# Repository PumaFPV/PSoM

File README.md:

# PSoM
PSoM, either Pico System On Module, or Puma System On Module for those who prefer.

The goal is to have an easy to integrate MCU + BMS for any kind of projects.
Without attaching points, the SoM is 20mm*20mm. 

## PSoM_ESP32S2_00
Hardware is done and working!

## PSoM_RP2040_00
Schematic is work in progress

##PSoM_ESP32_PICOD4_00
Schematic os work on progress

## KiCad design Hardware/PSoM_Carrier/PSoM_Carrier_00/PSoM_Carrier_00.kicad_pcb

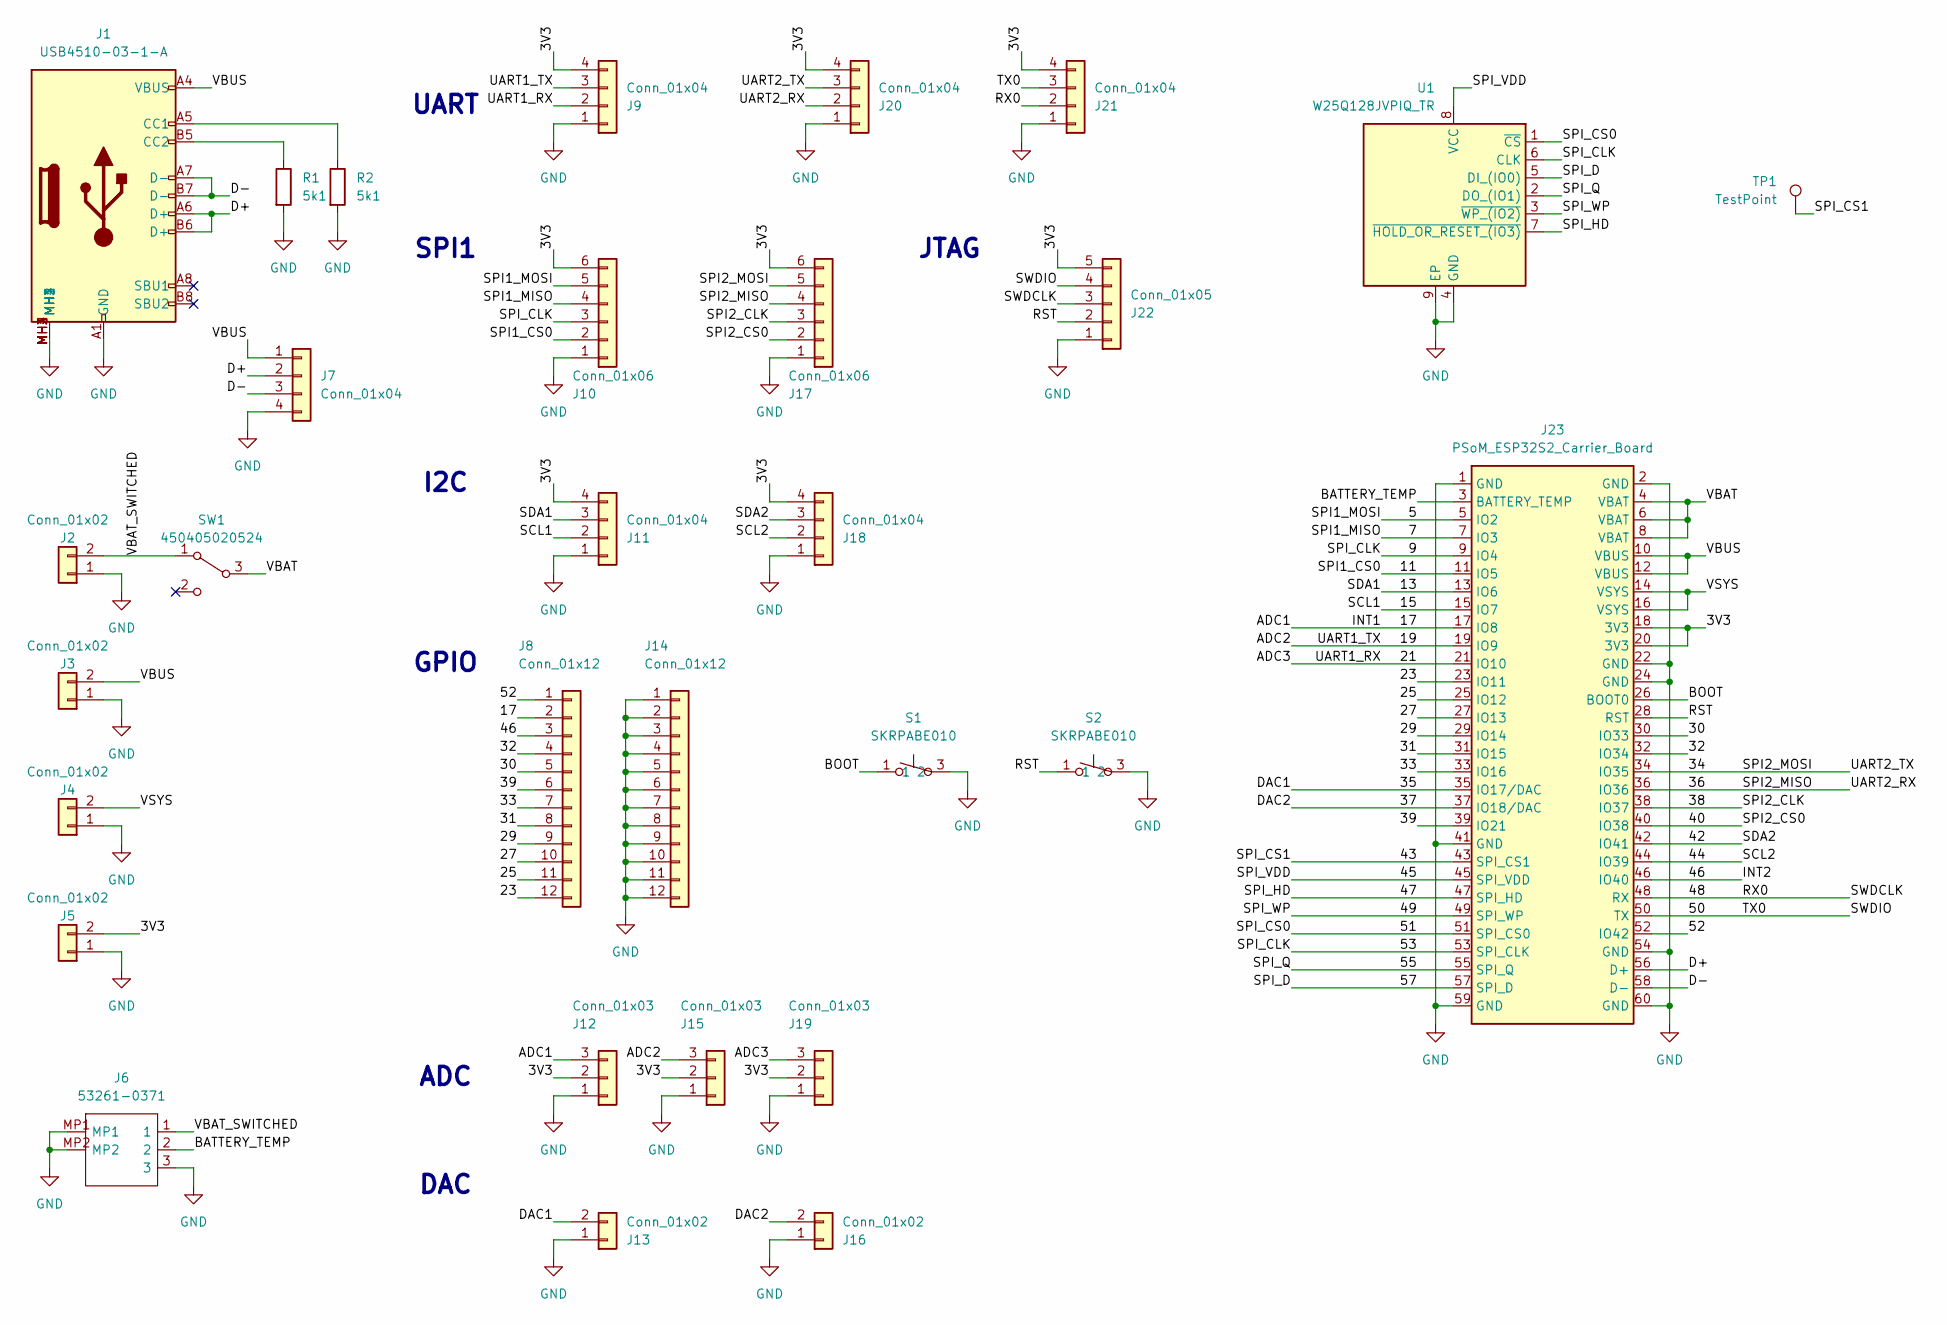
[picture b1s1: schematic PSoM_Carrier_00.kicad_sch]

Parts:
J1: USB4510-03-1-A; USB4510031A; Mouser Part Number 640-USB4510031A
J2, J3, J4, J5, J13, J16: Conn_01x02; PinHeader_1x02_P2.54mm_Vertical
J6: 53261-0371; 532610371; Mouser Part Number 538-53261-0371
J7, J9, J11, J18, J20, J21: Conn_01x04; PinHeader_1x04_P2.54mm_Vertical
J8, J14: Conn_01x12; PinHeader_1x12_P2.54mm_Vertical
J10, J17: Conn_01x06; PinHeader_1x06_P2.54mm_Vertical
J12, J15, J19: Conn_01x03; PinHeader_1x03_P2.54mm_Vertical
J22: Conn_01x05; PinHeader_1x05_P2.54mm_Vertical
J23: PSoM_ESP32S2_Carrier_Board; PSoM_ESP32S2_00
R1, R2: 5k1; R_0402_1005Metric
S1, S2: SKRPABE010; Mouser Part Number 688-SKRPAB
SW1: 450405020524
TP1: TestPoint; TestPoint_Pad_1.0x1.0mm
U1: W25Q128JVPIQ_TR; SON127P600X500X80-9N-D; Mouser Part Number 454-W25Q128JVPIQTR

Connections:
/3V3: J5.2, J9.4, J10.6, J11.4, J12.2, J15.2, J17.6, J18.4, J19.2, J20.4, J21.4, J22.5, J23.18 (3V3), J23.20 (3V3)
/5: J10.5, J23.5 (IO2)
/7: J10.4, J23.7 (IO3)
/11: J10.2, J23.11 (IO5)
/13: J11.3, J23.13 (IO6)
/15: J11.2, J23.15 (IO7)
/17: J8.2, J12.3, J23.17 (IO8)
/19: J9.3, J15.3, J23.19 (IO9)
/21: J9.2, J19.3, J23.21 (IO10)
/23: J8.12, J23.23 (IO11)
/25: J8.11, J23.25 (IO12)
/27: J8.10, J23.27 (IO13)
/29: J8.9, J23.29 (IO14)
/30: J8.5, J23.30 (IO33)
/31: J8.8, J23.31 (IO15)
/32: J8.4, J23.32 (IO34)
/33: J8.7, J23.33 (IO16)
/34: J17.5, J20.3, J23.34 (IO35)
/35: J13.2, J23.35 (IO17/DAC)
/36: J17.4, J20.2, J23.36 (IO36)
/37: J16.2, J23.37 (IO18/DAC)
/38: J17.3, J23.38 (IO37)
/39: J8.6, J23.39 (IO21)
/40: J17.2, J23.40 (IO38)
/42: J18.3, J23.42 (IO41)
/43: J23.43 (SPI_CS1), TP1.1; also elsewhere on the board
/44: J18.2, J23.44 (IO39)
/45: J23.45 (SPI_VDD), U1.8 (VCC)
/46: J8.3, J23.46 (IO40)
/47: J23.47 (SPI_HD), U1.7 (~HOLD_OR_RESET_(IO3))
/48: J21.2, J22.3, J23.48 (RX)
/49: J23.49 (SPI_WP), U1.3 (~WP_(IO2))
/50: J21.3, J22.4, J23.50 (TX)
/51: J23.51 (SPI_CS0), U1.1 (~CS)
/52: J8.1, J23.52 (IO42)
/53: J10.3, J23.9 (IO4), J23.53 (SPI_CLK), U1.6 (CLK)
/55: J23.55 (SPI_Q), U1.2 (DO_(IO1))
/57: J23.57 (SPI_D), U1.5 (DI_(IO0))
/BATTERY_TEMP: J6.2, J23.3 (BATTERY_TEMP)
/BOOT: J23.26 (BOOT0), S1.1, S1.2 (1)
/D+: J1.A6 (D+), J1.B6 (D+), J7.2, J23.56 (D+)
/D-: J1.A7 (D-), J1.B7 (D-), J7.3, J23.58 (D-)
/RST: J22.2, J23.28 (RST), S2.1, S2.2 (1)
/VBAT: J23.4 (VBAT), J23.6 (VBAT), J23.8 (VBAT), SW1.3 (B)
/VBAT_SWITCHED: J2.2, J6.1, SW1.1 (A)
/VBUS: J1.A4 (VBUS), J1.A9 (VBUS), J1.B4 (VBUS), J1.B9 (VBUS), J3.2, J7.1, J23.10 (VBUS), J23.12 (VBUS)
/VSYS: J4.2, J23.14 (VSYS), J23.16 (VSYS)
GND: J1.A1 (GND), J1.A12 (GND), J1.B1 (GND), J1.B12 (GND), J1.MH1, J1.MH2, J1.MH3, J1.MH4, J2.1, J3.1, J4.1, J5.1, J6.3, J6.MP1, J6.MP2, J7.4, J9.1, J10.1, J11.1, J12.1, J13.1, J14.1, J14.2, J14.3, J14.4, J14.5, J14.6, J14.7, J14.8, J14.9, J14.10, J14.11, J14.12, J15.1, J16.1, J17.1, J18.1, J19.1, J20.1, J21.1, J22.1, J23.1 (GND), J23.2 (GND), J23.22 (GND), J23.24 (GND), J23.41 (GND), J23.54 (GND), J23.59 (GND), J23.60 (GND), R1.2, R2.2, S1.3 (2), S1.4 (2), S2.3 (2), S2.4 (2), U1.4 (GND), U1.9 (EP)
unnamed: J1.A5 (CC1), R2.1
unnamed: J1.B5 (CC2), R1.1

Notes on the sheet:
ADC
DAC
I2C
JTAG
SPI1
GPIO
UART

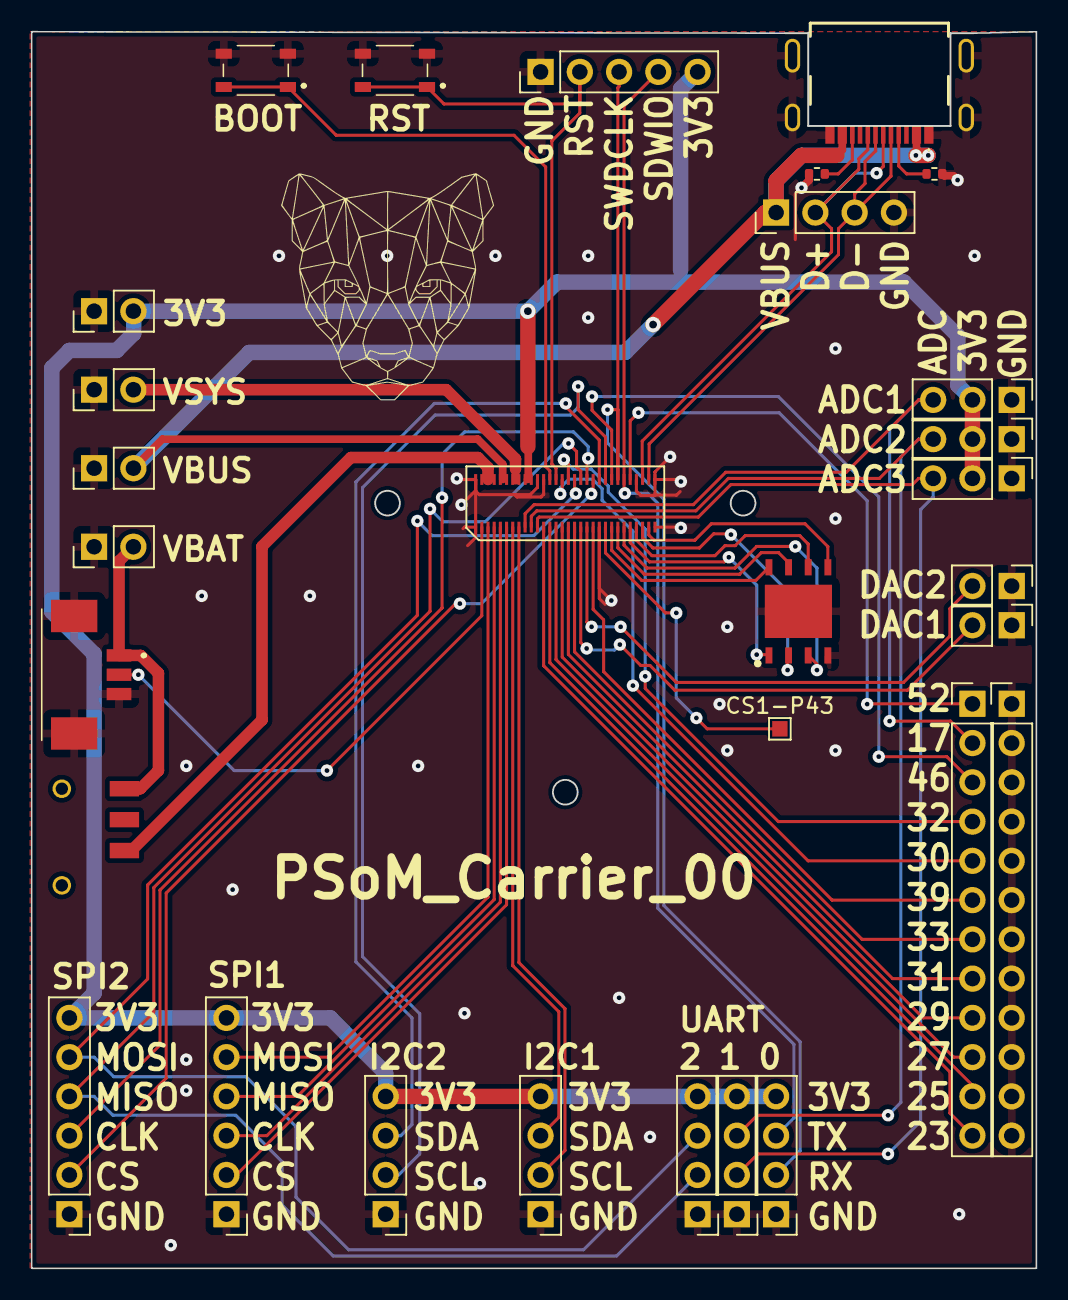
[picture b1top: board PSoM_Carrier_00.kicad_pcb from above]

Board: 2 copper layers, 65.0 x 80.0 mm, 30 parts (0 on the bottom side), 50 nets.

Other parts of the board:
CS1-P43: TestPoint; TestPoint_Pad_1.0x1.0mm

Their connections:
/43: CS1-P43.1; also elsewhere on the board

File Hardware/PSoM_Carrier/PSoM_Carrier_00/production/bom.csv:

Designator,Footprint,Quantity,Value,LCSC Part #
CS1-P43,TestPoint_Pad_1.0x1.0mm,1,TestPoint,
J1,USB4510031A,1,USB4510-03-1-A,
"J10, J17",PinHeader_1x06_P2.54mm_Vertical,2,Conn_01x06,
"J11, J18, J20, J21, J7, J9",PinHeader_1x04_P2.54mm_Vertical,6,Conn_01x04,
"J12, J15, J19",PinHeader_1x03_P2.54mm_Vertical,3,Conn_01x03,
"J13, J16, J2, J3, J4, J5",PinHeader_1x02_P2.54mm_Vertical,6,Conn_01x02,
"J14, J8",PinHeader_1x12_P2.54mm_Vertical,2,Conn_01x12,
J22,PinHeader_1x05_P2.54mm_Vertical,1,Conn_01x05,
J23,PSoM_ESP32S2_00,1,PSoM_ESP32S2_Carrier_Board,
J6,532610371,1,53261-0371,
"R1, R2",0402,2,5k1,
"S1, S2",SKRPABE010,2,SKRPABE010,
SW1,450405020524,1,450405020524,
U1,SON127P600X500X80-9N-D,1,W25Q128JVPIQ_TR,

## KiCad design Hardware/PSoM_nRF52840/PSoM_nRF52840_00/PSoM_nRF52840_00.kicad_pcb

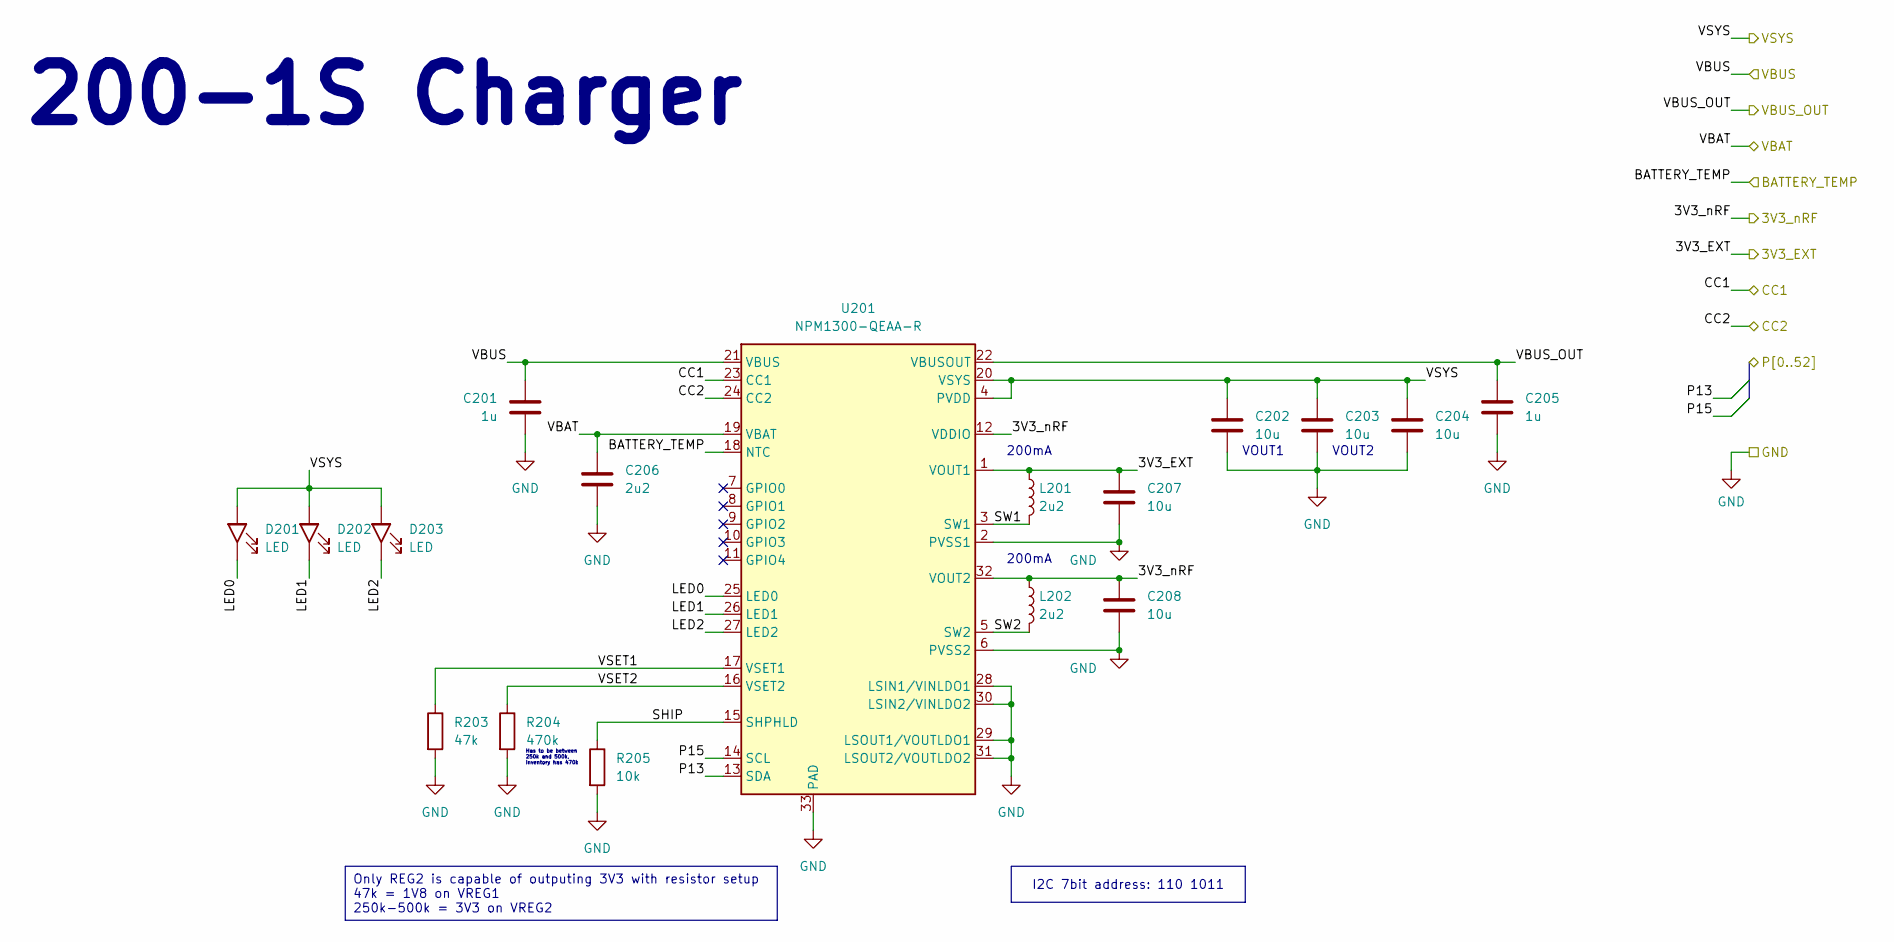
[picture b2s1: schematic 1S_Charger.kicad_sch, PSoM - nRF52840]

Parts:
C201, C205: 1u; C_0402_1005Metric
C202, C203, C204: 10u; C_0603_1608Metric
C206: 2u2; C_0603_1608Metric
C207: 10u; C_0402_1005Metric
C208: 10u; C_0402_1005Metric_Pad0.74x0.62mm_HandSolder
D201, D202, D203: LED; LED_0402_1005Metric
L201, L202: 2u2; L_0603_1608Metric
R203: 47k; R_0201_0603Metric
R204: 470k; R_0201_0603Metric
R205: 10k; R_0201_0603Metric
U201: NPM1300-QEAA-R; Mouser Part Number 949-NPM1300-QEAA-R

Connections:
+3V3: C207.1, L201.1, U201.1 (VOUT1); also elsewhere on the board
/100_Connectors/BATTERY_TEMP: U201.18 (NTC); also elsewhere on the board
/100_Connectors/CC1: U201.23 (CC1); also elsewhere on the board
/100_Connectors/CC2: U201.24 (CC2); also elsewhere on the board
/100_Connectors/VBAT: C206.1, U201.19 (VBAT); also elsewhere on the board
/100_Connectors/VSYS: C202.1, C203.1, C204.1, D201.1 (A), D202.1 (A), D203.1 (A), U201.4 (PVDD), U201.20 (VSYS); also elsewhere on the board
/200_1S_Charger/3V3_nRF: C208.1, L202.1, U201.12 (VDDIO), U201.32 (VOUT2); also elsewhere on the board
/200_1S_Charger/LED0: D201.2 (K), U201.25 (LED0)
/200_1S_Charger/LED1: D202.2 (K), U201.26 (LED1)
/200_1S_Charger/LED2: D203.2 (K), U201.27 (LED2)
/200_1S_Charger/SHIP: R205.1, U201.15 (SHPHLD)
/200_1S_Charger/SW1: L201.2, U201.3 (SW1)
/200_1S_Charger/SW2: L202.2, U201.5 (SW2)
/200_1S_Charger/VBUS_OUT: C205.1, U201.22 (VBUSOUT); also elsewhere on the board
/200_1S_Charger/VSET1: R203.1, U201.17 (VSET1)
/200_1S_Charger/VSET2: R204.1, U201.16 (VSET2)
GND: C201.1, C202.2, C203.2, C204.2, C205.2, C206.2, C207.2, C208.2, R203.2, R204.2, R205.2, U201.2 (PVSS1), U201.6 (PVSS2), U201.28 (LSIN1/VINLDO1), U201.29 (LSOUT1/VOUTLDO1), U201.30 (LSIN2/VINLDO2), U201.31 (LSOUT2/VOUTLDO2), U201.33 (PAD); also elsewhere on the board
P13: U201.13 (SDA); also elsewhere on the board
P15: U201.14 (SCL); also elsewhere on the board
VBUS: C201.2, U201.21 (VBUS); also elsewhere on the board

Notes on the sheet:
Only REG2 is capable of outputing 3V3 with resistor setup 47k = 1V8 on VREG1 250k-500k = 3V3 on VREG2
I2C 7bit address: 110 1011
200-1S Charger
200mA
Has to be between 250k and 500k, Inventory has 470k
VOUT1
VOUT2

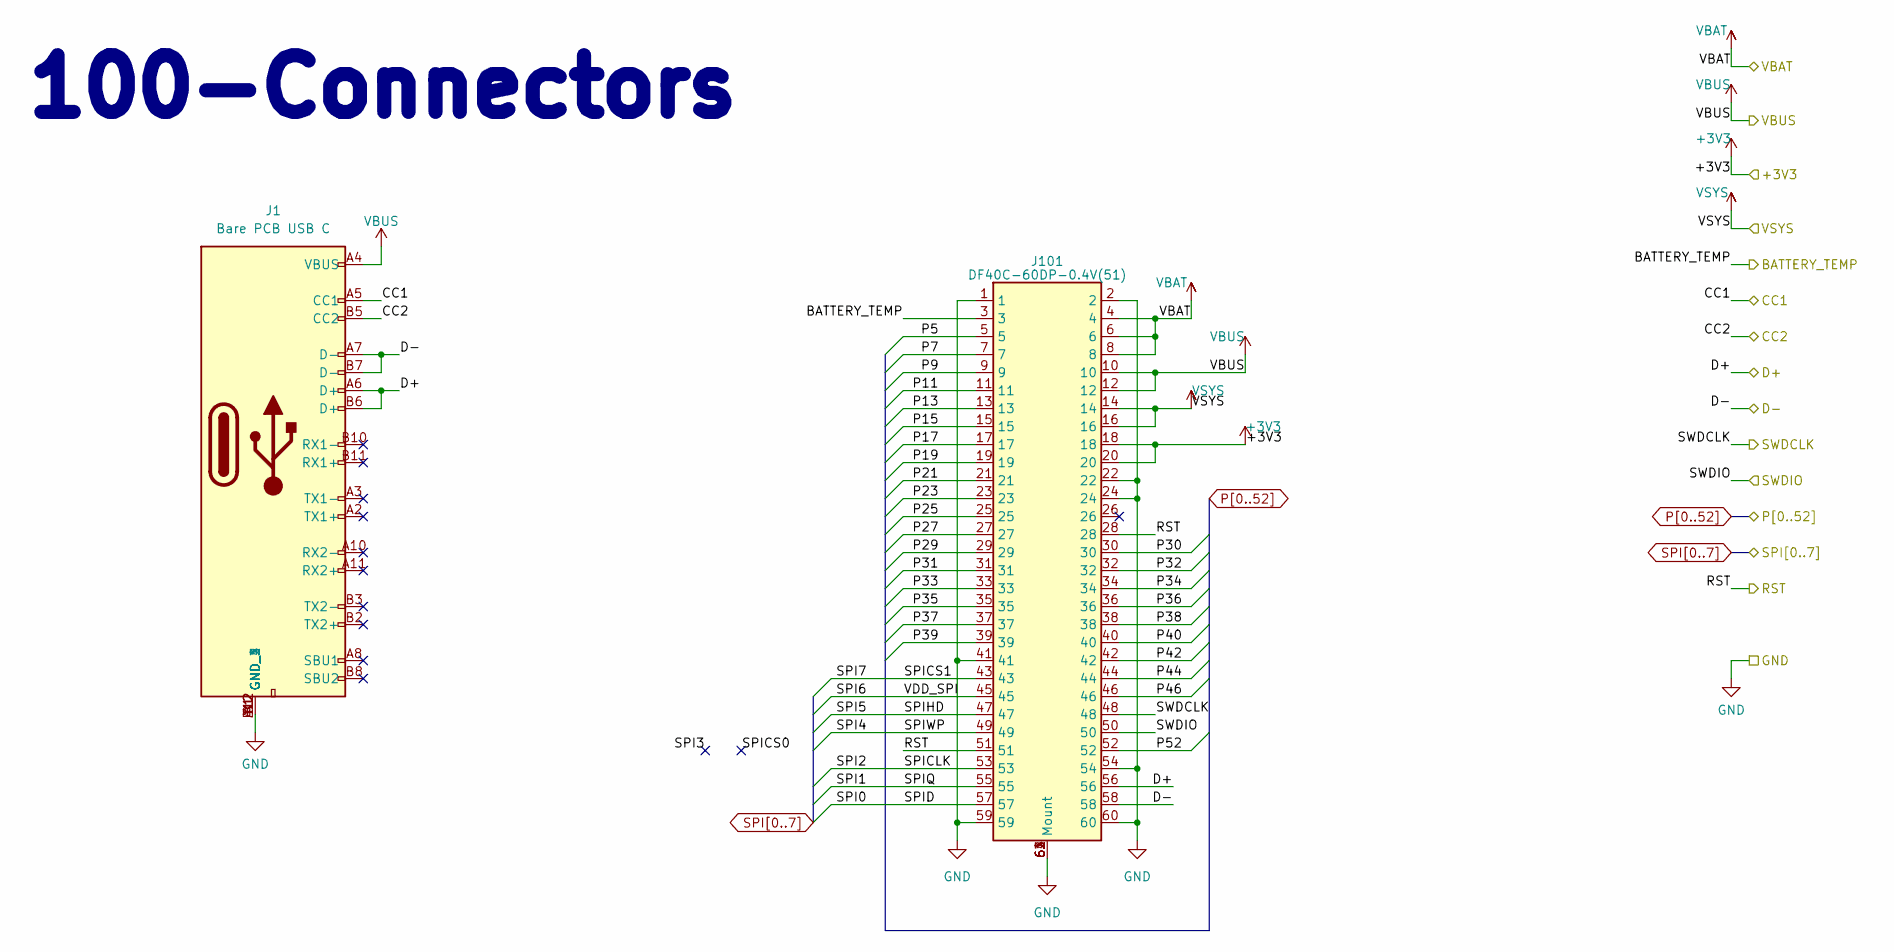
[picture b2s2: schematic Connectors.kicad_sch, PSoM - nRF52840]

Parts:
J1: Bare PCB USB C; usb-c-pcb; Mouser Part Number 640-USB4510031A
J101: DF40C-60DP-0.4V(51)

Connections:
+3V3: J101.18, J101.20; also elsewhere on the board
/100_Connectors/BATTERY_TEMP: J101.3; also elsewhere on the board
/100_Connectors/CC1: J1.A5 (CC1); also elsewhere on the board
/100_Connectors/CC2: J1.B5 (CC2); also elsewhere on the board
/100_Connectors/D+: J1.A6 (D+), J1.B6 (D+), J101.56; also elsewhere on the board
/100_Connectors/D-: J1.A7 (D-), J1.B7 (D-), J101.58; also elsewhere on the board
/100_Connectors/RST: J101.28, J101.51; also elsewhere on the board
/100_Connectors/SWDCLK: J101.48; also elsewhere on the board
/100_Connectors/SWDIO: J101.50; also elsewhere on the board
/100_Connectors/VBAT: J101.4, J101.6, J101.8; also elsewhere on the board
/100_Connectors/VSYS: J101.14, J101.16; also elsewhere on the board
GND: J1.A1 (GND_1), J1.A12 (GND_2), J1.B1 (GND_3), J1.B12 (GND_4), J101.1, J101.2, J101.22, J101.24, J101.41, J101.54, J101.59, J101.60, J101.61 (Mount), J101.62, J101.63, J101.64; also elsewhere on the board
P5: J101.5; also elsewhere on the board
P7: J101.7; also elsewhere on the board
P9: J101.9; also elsewhere on the board
P11: J101.11; also elsewhere on the board
P13: J101.13; also elsewhere on the board
P15: J101.15; also elsewhere on the board
P17: J101.17; also elsewhere on the board
P19: J101.19; also elsewhere on the board
P21: J101.21; also elsewhere on the board
P23: J101.23; also elsewhere on the board
P25: J101.25; also elsewhere on the board
P27: J101.27; also elsewhere on the board
P29: J101.29; also elsewhere on the board
P30: J101.30; also elsewhere on the board
P31: J101.31; also elsewhere on the board
P32: J101.32; also elsewhere on the board
P33: J101.33; also elsewhere on the board
P34: J101.34; also elsewhere on the board
P35: J101.35; also elsewhere on the board
P36: J101.36; also elsewhere on the board
P37: J101.37; also elsewhere on the board
P38: J101.38; also elsewhere on the board
P39: J101.39; also elsewhere on the board
P40: J101.40; also elsewhere on the board
P42: J101.42; also elsewhere on the board
P44: J101.44; also elsewhere on the board
P46: J101.46; also elsewhere on the board
P52: J101.52; also elsewhere on the board
SPI0: J101.57; also elsewhere on the board
SPI1: J101.55; also elsewhere on the board
SPI2: J101.53; also elsewhere on the board
SPI4: J101.49; also elsewhere on the board
SPI5: J101.47; also elsewhere on the board
SPI6: J101.45
SPI7: J101.43; also elsewhere on the board
VBUS: J1.A4 (VBUS), J1.A9 (VBUS), J1.B4 (VBUS), J1.B9 (VBUS), J101.10, J101.12; also elsewhere on the board

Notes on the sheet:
100-Connectors

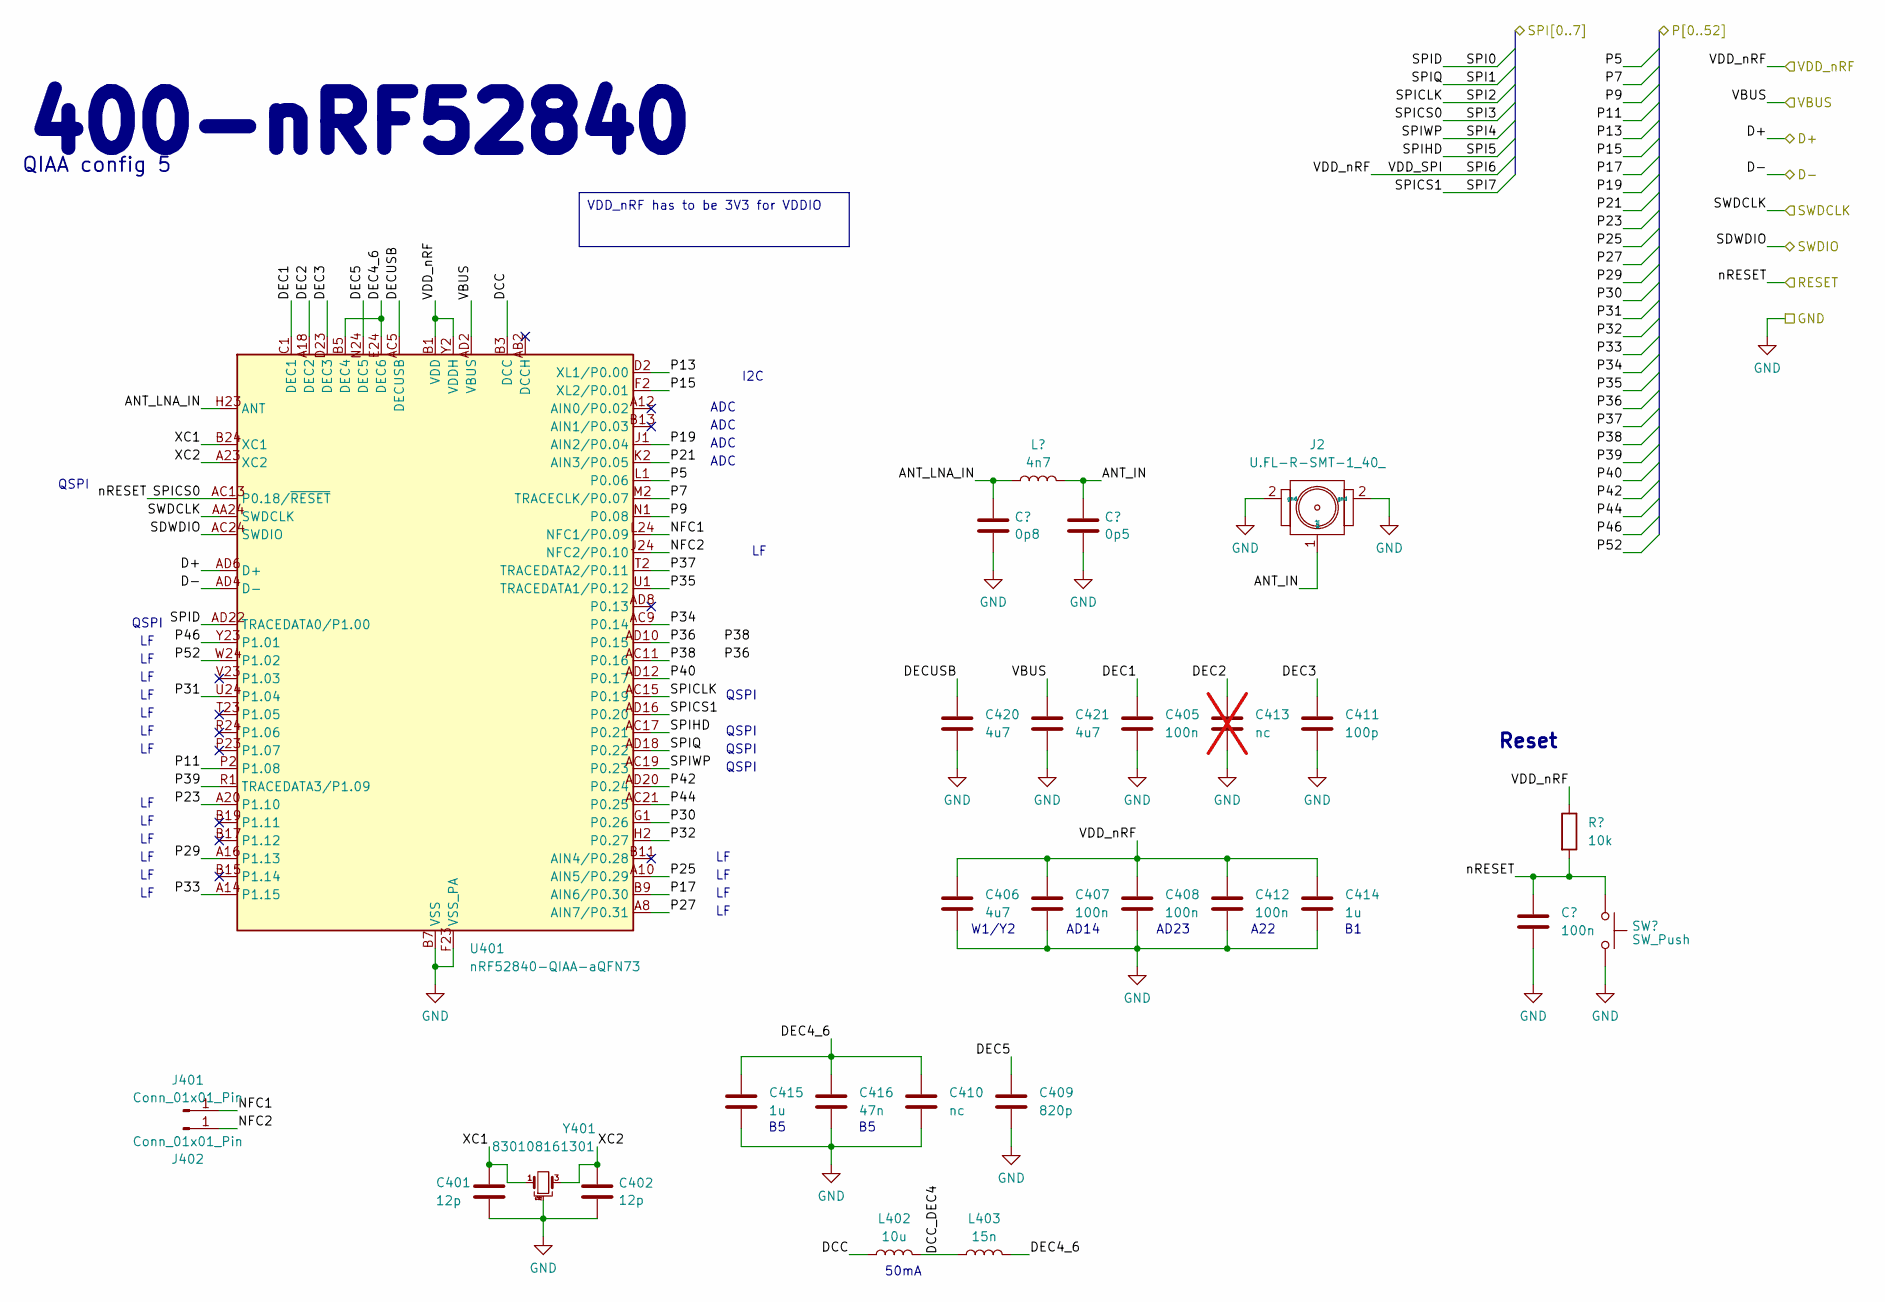
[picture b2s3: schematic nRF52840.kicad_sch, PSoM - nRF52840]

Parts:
C401, C402: 12p; C_0201_0603Metric
C403: 0p8; C_0201_0603Metric
C404: 0p5; C_0201_0603Metric
C405, C407, C408, C412, C461: 100n; C_0201_0603Metric
C406, C420, C421: 4u7; C_0603_1608Metric
C409: 820p; C_0201_0603Metric
C410: nc; C_0402_1005Metric
C411: 100p; C_0201_0603Metric
C413: nc; C_0402_1005Metric; not fitted
C414, C415: 1u; C_0402_1005Metric
C416: 47n; C_0402_1005Metric
J2: U.FL-R-SMT-1_40_; u.fl; Mouser Part Number 798-UFLRSMT140
J401, J402: Conn_01x01_Pin; SolderWirePad_1x01_SMD_1x2mm
L401: 4n7; L_0201_0603Metric
L402: 10u; L_0603_1608Metric
L403: 15n; L_0402_1005Metric
R461: 10k; R_0201_0603Metric
SW461: SW_Push; B3U-1000P
U401: nRF52840-QIAA-aQFN73; Nordic_AQFN-73-1EP_7x7mm_P0.5mm
Y401: 830108161301; 830108161301_1.6x1.2mm

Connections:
/100_Connectors/D+: U401.AD6 (D+); also elsewhere on the board
/100_Connectors/D-: U401.AD4 (D-); also elsewhere on the board
/100_Connectors/RST: C461.1, R461.2, SW461.1, U401.AC13 (P0.18/~RESET); also elsewhere on the board
/100_Connectors/SWDCLK: U401.AA24 (SWDCLK); also elsewhere on the board
/100_Connectors/SWDIO: U401.AC24 (SWDIO); also elsewhere on the board
/200_1S_Charger/3V3_nRF: C406.1, C407.1, C408.1, C412.1, C414.1, R461.1, U401.A22 (VDD), U401.AD14 (VDD), U401.AD23 (VDD), U401.B1 (VDD), U401.W1 (VDD), U401.Y2 (VDDH); also elsewhere on the board
/200_1S_Charger/VBUS_OUT: C421.1, U401.AD2 (VBUS); also elsewhere on the board
/400-nRF52840/ANT_IN: C404.1, J2.1 (ant), L401.1
/400-nRF52840/ANT_LNA_IN: C403.1, L401.2, U401.H23 (ANT)
/400-nRF52840/DCC: L402.1, U401.B3 (DCC)
/400-nRF52840/DCC_DEC4: L402.2, L403.1
/400-nRF52840/DEC1: C405.1, U401.C1 (DEC1)
/400-nRF52840/DEC2: C413.1, U401.A18 (DEC2)
/400-nRF52840/DEC3: C411.1, U401.D23 (DEC3)
/400-nRF52840/DEC4_6: C410.1, C415.1, C416.1, L403.2, U401.B5 (DEC4), U401.E24 (DEC6)
/400-nRF52840/DEC5: C409.1, U401.N24 (DEC5)
/400-nRF52840/DECUSB: C420.1, U401.AC5 (DECUSB)
/400-nRF52840/NFC1: J401.1, U401.L24 (NFC1/P0.09)
/400-nRF52840/NFC2: J402.1, U401.J24 (NFC2/P0.10)
/400-nRF52840/XC1: C401.1, U401.B24 (XC1), Y401.1
/400-nRF52840/XC2: C402.1, U401.A23 (XC2), Y401.3
GND: C401.2, C402.2, C403.2, C404.2, C405.2, C406.2, C407.2, C408.2, C409.2, C410.2, C411.2, C412.2, C413.2, C414.2, C415.2, C416.2, C420.2, C421.2, C461.2, J2.2 (gnd), SW461.2, U401.B7 (VSS), U401.EP (VSS), U401.F23 (VSS_PA), Y401.2, Y401.4; also elsewhere on the board
P5: U401.L1 (P0.06); also elsewhere on the board
P7: U401.M2 (TRACECLK/P0.07); also elsewhere on the board
P9: U401.N1 (P0.08); also elsewhere on the board
P11: U401.P2 (P1.08); also elsewhere on the board
P13: U401.D2 (XL1/P0.00); also elsewhere on the board
P15: U401.F2 (XL2/P0.01); also elsewhere on the board
P17: U401.B9 (AIN6/P0.30); also elsewhere on the board
P19: U401.J1 (AIN2/P0.04); also elsewhere on the board
P21: U401.K2 (AIN3/P0.05); also elsewhere on the board
P23: U401.A20 (P1.10); also elsewhere on the board
P25: U401.A10 (AIN5/P0.29); also elsewhere on the board
P27: U401.A8 (AIN7/P0.31); also elsewhere on the board
P29: U401.A16 (P1.13); also elsewhere on the board
P30: U401.G1 (P0.26); also elsewhere on the board
P31: U401.U24 (P1.04); also elsewhere on the board
P32: U401.H2 (P0.27); also elsewhere on the board
P33: U401.A14 (P1.15); also elsewhere on the board
P34: U401.AC9 (P0.14); also elsewhere on the board
P35: U401.U1 (TRACEDATA1/P0.12); also elsewhere on the board
P36: U401.AD10 (P0.15); also elsewhere on the board
P37: U401.T2 (TRACEDATA2/P0.11); also elsewhere on the board
P38: U401.AC11 (P0.16); also elsewhere on the board
P39: U401.R1 (TRACEDATA3/P1.09); also elsewhere on the board
P40: U401.AD12 (P0.17); also elsewhere on the board
P42: U401.AD20 (P0.24); also elsewhere on the board
P44: U401.AC21 (P0.25); also elsewhere on the board
P46: U401.Y23 (P1.01); also elsewhere on the board
P52: U401.W24 (P1.02); also elsewhere on the board
SPI0: U401.AD22 (TRACEDATA0/P1.00); also elsewhere on the board
SPI1: U401.AD18 (P0.22); also elsewhere on the board
SPI2: U401.AC15 (P0.19); also elsewhere on the board
SPI4: U401.AC19 (P0.23); also elsewhere on the board
SPI5: U401.AC17 (P0.21); also elsewhere on the board
SPI7: U401.AD16 (P0.20); also elsewhere on the board

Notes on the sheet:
VDD_nRF has to be 3V3 for VDDIO
I2C
ADC
AD23
QSPI
Reset
A22
400-nRF52840
50mA
W1/Y2
AD14
QIAA config 5

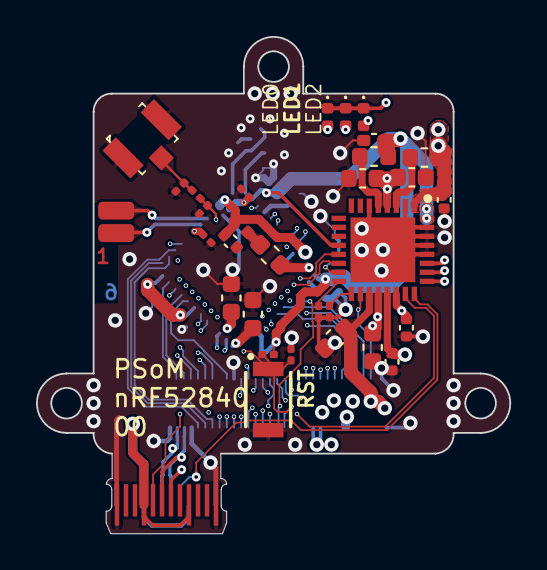
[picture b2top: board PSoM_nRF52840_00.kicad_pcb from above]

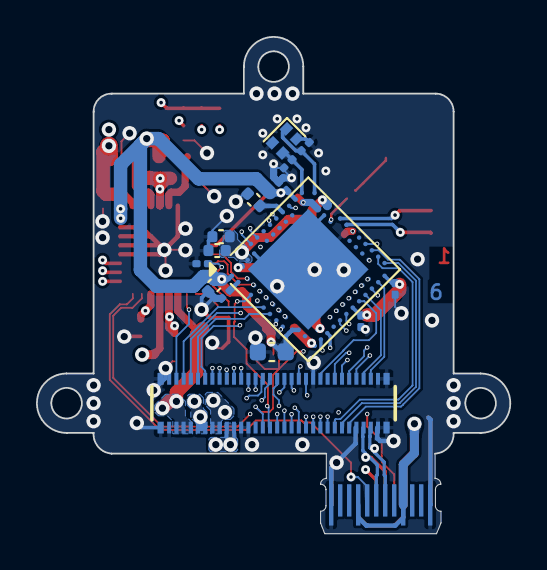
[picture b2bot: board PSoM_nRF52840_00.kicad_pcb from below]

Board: 6 copper layers, 26.3 x 27.6 mm, 48 parts (15 on the bottom side), 71 nets.

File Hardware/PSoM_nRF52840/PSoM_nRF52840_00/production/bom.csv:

Designator,Footprint,Quantity,Value,LCSC Part #
"C201, C205, C414, C415",0402,4,1u,
"C202, C203, C204, L402",0603,4,10u,
"C206, L201, L202",0603,3,2u2,
"C207, C208",0402,2,10u,
"C401, C402",0201,2,12p,
C403,0201,1,0p8,
C404,0201,1,0p5,
"C405, C407, C408, C412, C461",0201,5,100n,
"C406, C420, C421",0603,3,4u7,
C409,0201,1,820p,
"C410, C413",0402,2,nc,
C411,0201,1,100p,
C416,0402,1,47n,
"D201, D202, D203",0402,3,LED,
J1,usb-c-pcb,1,Bare PCB USB C,
J101,DF40C-60DP-0.4V(51),1,DF40C-60DP-0.4V(51),
J2,u.fl,1,U.FL-R-SMT-1_40_,
"J401, J402",SolderWirePad_1x01_SMD_1x2mm,2,Conn_01x01_Pin,
L401,0201,1,4n7,
L403,0402,1,15n,
R203,0201,1,47k,
R204,0201,1,470k,
"R205, R461",0201,2,10k,
SW461,B3U-1000P,1,SW_Push,
U201,NPM1300-QEAA-R,1,NPM1300-QEAA-R,
U401,Nordic_AQFN-73-1EP_7x7mm_P0.5mm,1,nRF52840-QIAA-aQFN73,
Y401,830108161301_1.6x1.2mm,1,830108161301,

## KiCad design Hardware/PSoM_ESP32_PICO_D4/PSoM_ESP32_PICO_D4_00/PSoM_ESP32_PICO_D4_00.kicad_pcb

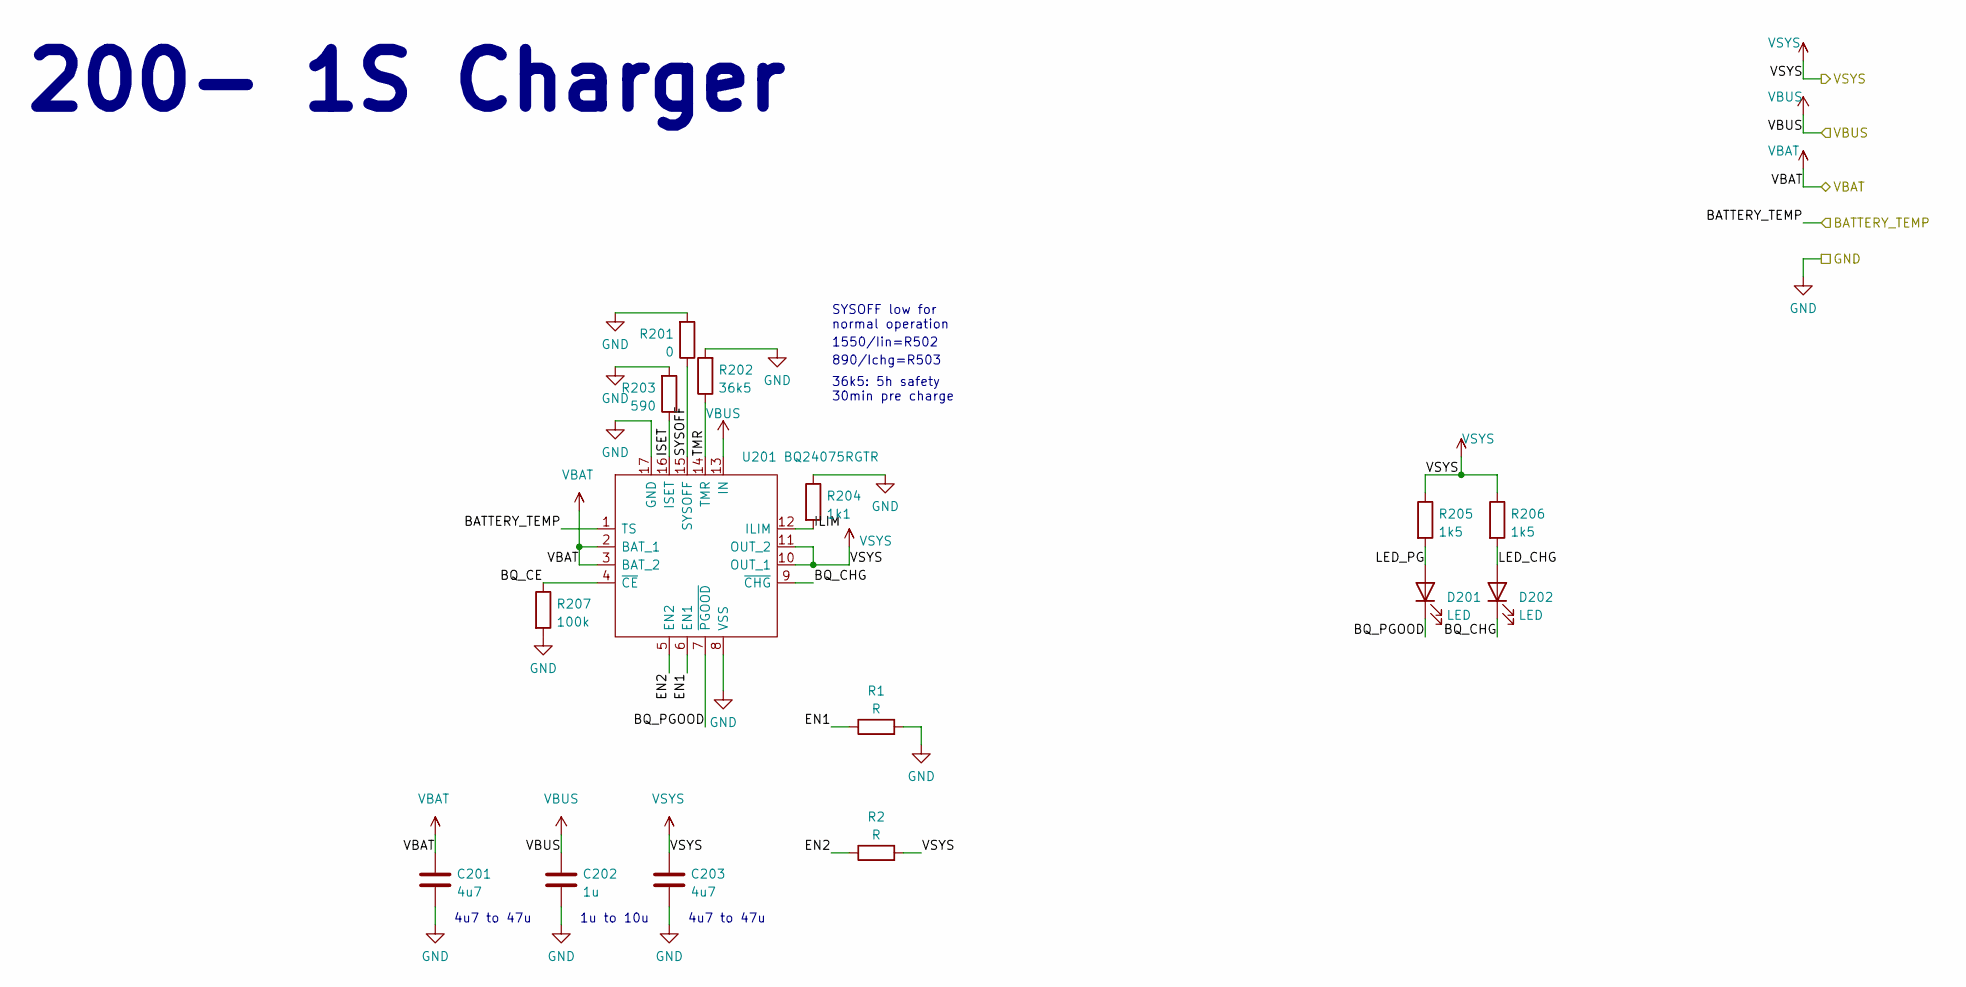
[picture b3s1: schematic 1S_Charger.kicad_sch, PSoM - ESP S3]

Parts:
C201, C203: 4u7; C_0603_1608Metric
C202: 1u; C_0603_1608Metric
D201, D202: LED; LED_0402_1005Metric
R1, R2: R; R_0402_1005Metric
R201: 0; R_0402_1005Metric
R202: 36k5; R_0402_1005Metric
R203: 590; R_0402_1005Metric
R204: 1k1; R_0402_1005Metric
R205, R206: 1k5; R_0402_1005Metric
R207: 100k; R_0402_1005Metric
U201: BQ24075RGTR; QFN50P300X300X100-17N-D; Mouser Part Number 595-BQ24075RGTR

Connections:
/100_Connectors/BATTERY_TEMP: U201.1 (TS); also elsewhere on the board
/200_1S_Charger/BQ_CE: R207.1, U201.4 (~CE)
/200_1S_Charger/BQ_CHG: D202.1 (K), U201.9 (~CHG)
/200_1S_Charger/BQ_PGOOD: D201.1 (K), U201.7 (~PGOOD)
/200_1S_Charger/EN1: R1.1, U201.6 (EN1)
/200_1S_Charger/EN2: R2.1, U201.5 (EN2)
/200_1S_Charger/ILIM: R204.2, U201.12 (ILIM)
/200_1S_Charger/ISET: R203.1, U201.16 (ISET)
/200_1S_Charger/LED_CHG: D202.2 (A), R206.2
/200_1S_Charger/LED_PG: D201.2 (A), R205.2
/200_1S_Charger/SYSOFF: R201.1, U201.15 (SYSOFF)
/200_1S_Charger/TMR: R202.1, U201.14 (TMR)
/VBAT: C201.1, U201.2 (BAT_1), U201.3 (BAT_2); also elsewhere on the board
/VSYS: C203.1, R2.2, R205.1, R206.1, U201.10 (OUT_1), U201.11 (OUT_2); also elsewhere on the board
GND: C201.2, C202.2, C203.2, R1.2, R201.2, R202.2, R203.2, R204.1, R207.2, U201.8 (VSS), U201.17 (GND); also elsewhere on the board
VBUS: C202.1, U201.13 (IN); also elsewhere on the board

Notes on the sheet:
890/Ichg=R503
200- 1S Charger
4u7 to 47u
1u to 10u
SYSOFF low for normal operation
36k5: 5h safety 30min pre charge
1550/Iin=R502
